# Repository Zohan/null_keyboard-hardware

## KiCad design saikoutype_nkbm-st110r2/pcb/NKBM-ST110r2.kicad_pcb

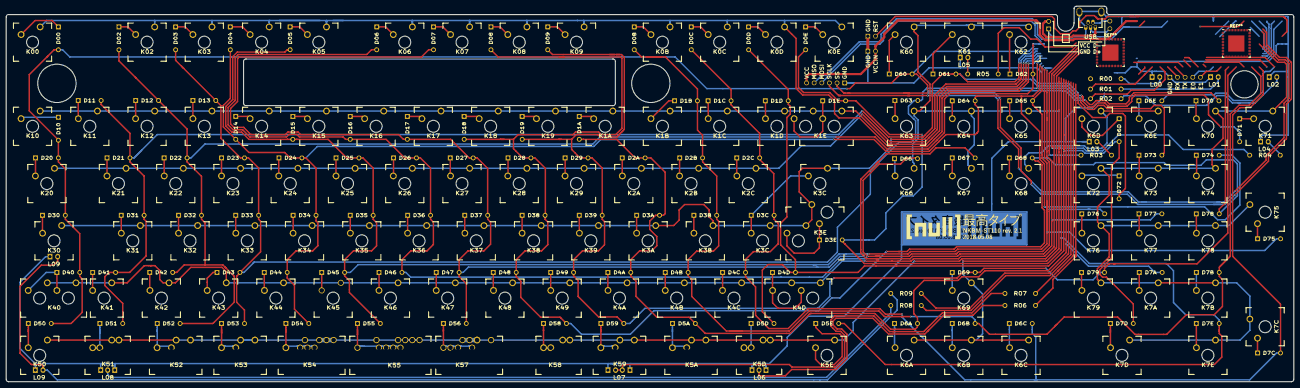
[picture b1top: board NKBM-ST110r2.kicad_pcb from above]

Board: 2 copper layers, 428.4 x 124.9 mm, 273 parts (0 on the bottom side), 146 nets.

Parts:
D00, D0B, D0C, D0D, D0E, D1A, D1B, D1C, D1D, D1E, D02, D2A, D2B, D2C, D03, D3A, D3B, D3C, D3E, D04, D4A, D4B, D4C, D4D, D05, D5A, D5D, D5E, D06, D6A, D6B, D6C, D6D, D6E, D07, D7A, D7B, D7C, D7D, D7E, D08, D09, D10, D11, D12, D13, D14, D15, D16, D17, D18, D19, D20, D21, D22, D23, D24, D25, D26, D27, D28, D29, D30, D31, D32, D33, D34, D35, D36, D37, D38, D39, D40, D41, D42, D43, D44, D45, D46, D47, D48, D49, D50, D51, D52, D53, D54, D55, D56, D58, D59, D60, D61, D62, D63, D64, D65, D66, D67, D68, D69, D70, D71, D72, D73, D74, D75, D76, D77, D78, D79: 1N4148; DIODE
EXPANSION: HEADER; TEENSY2.0++
K00, K0B, K0C, K0D, K0E, K1A, K1B, K1C, K1D, K1E2, K02, K2A, K2B, K2C, K03, K3A, K3B, K04, K4A, K4B, K4C, K05, K5D, K06, K6A, K6B, K6C, K6D, K6E, K07, K7A, K7B, K7E, K08, K09, K10, K11, K12, K13, K14, K15, K16, K17, K18, K19, K21, K22, K23, K24, K25, K26, K27, K28, K29, K31, K32, K33, K34, K35, K36, K37, K38, K39, K41, K42, K43, K44, K46, K47, K48, K49, K51, K53, K58#2, K60, K61, K62, K63, K64, K65, K66, K67, K68, K69, K70, K71, K72, K73, K74, K76, K77, K78, K79: CHRY_MX; CHERRY_PLATE_100H
K1E, K3E, K7D, K54, K57: CHRY_MX; CHERRY_PLATE_200H
K3C, K3C#2, K20: CHRY_MX; CHERRY_PLATE_150H
K3E2, K40, K542, K573: CHRY_MX; CHERRY_PLATE_225H
K4D, K30: CHRY_MX; CHERRY_PLATE_175H
K4D2: CHRY_MX; CHERRY_PLATE_275H
K5A, K5A1, K5D1, K5E, K45, K50, K52, K58, K59, K402, K511, K521, K521#2, K521#3, K541, K551, K553, K553#2, K572, K572#2, K591: CHRY_MX; CHERRY_PLATE_125H
K7C, K75: CHRY_MX; CHERRY_PLATE_200V
K55: CHRY_MX; CHERRY_PLATE_625H
K552: CHRY_MX; CHERRY_PLATE_450H
L00, L01, L02, L03, L04, L05, L07, L07#2, L09, L09#2: LED; LED_3MM
L06, L08: LED; LED_3MM1
R00, R01, R02, R03, R04, R05, R06, R07, R08, R09: R; RESISTOR
RST: HEADER; TEENSY2.0++
SPI: HEADER; TEENSY2.0++
USB: Molex USB_Mini-B; USB_Mini-B_Lumberg_2486_01_Horizontal
USB DATA: BREAKOUT; TEENSY2.0++
USB POWER: BREAKOUT; TEENSY2.0++
VCCIN: HEADER; TEENSY2.0++

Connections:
/COL_00: D00.2, D10.2, D20.2, D30.2, D40.2, D50.2, D60.2, D70.2
/COL_01: D11.2, D21.2, D31.2, D41.2, D51.2, D61.2, D71.2
/COL_02: D02.2, D12.2, D22.2, D32.2, D42.2, D52.2, D62.2, D72.2
/COL_03: D03.2, D13.2, D23.2, D33.2, D43.2, D53.2, D63.2, D73.2
/COL_04: D04.2, D14.2, D24.2, D34.2, D44.2, D54.2, D64.2, D74.2
/COL_05: D05.2, D15.2, D25.2, D35.2, D45.2, D55.2, D65.2, D75.2
/COL_06: D06.2, D16.2, D26.2, D36.2, D46.2, D66.2, D76.2
/COL_07: D07.2, D17.2, D27.2, D37.2, D47.2, D56.2, D67.2, D77.2
/COL_08: D08.2, D18.2, D28.2, D38.2, D48.2, D58.2, D68.2, D78.2
/COL_09: D09.2, D19.2, D29.2, D39.2, D49.2, D59.2, D69.2, D79.2
/COL_10: D1A.2, D2A.2, D3A.2, D4A.2, D5A.2, D6A.2, D7A.2
/COL_11: D0B.2, D1B.2, D2B.2, D3B.2, D4B.2, D6B.2, D7B.2
/COL_12: D0C.2, D1C.2, D2C.2, D3C.2, D4C.2, D6C.2, D7C.2
/COL_13: D0D.2, D1D.2, D4D.2, D5D.2, D6D.2, D7D.2
/COL_14: D0E.2, D1E.2, D3E.2, D5E.2, D6E.2, D7E.2
/GND: EXPANSION.1, L00.1, L01.1, L02.1, L03.1, L04.1, L05.1, L06.1, L07.1, L07#2.1, L08.1, L09.1, L09#2.1, RST.1, SPI.6, USB.1, USB.6, USB.7, USB POWER.1, VCCIN.1
/ROW_00: K00.1, K0B.1, K0C.1, K0D.1, K0E.1, K02.1, K03.1, K04.1, K05.1, K06.1, K07.1, K08.1, K09.1
/ROW_01: K1A.1, K1B.1, K1C.1, K1D.1, K1E.1, K1E2.1, K10.1, K11.1, K12.1, K13.1, K14.1, K15.1, K16.1, K17.1, K18.1, K19.1
/ROW_02: K2A.1, K2B.1, K2C.1, K20.1, K21.1, K22.1, K23.1, K24.1, K25.1, K26.1, K27.1, K28.1, K29.1
/ROW_03: K3A.1, K3B.1, K3C.1, K3C#2.1, K3E.1, K3E2.1, K30.1, K31.1, K32.1, K33.1, K34.1, K35.1, K36.1, K37.1, K38.1, K39.1
/ROW_04: K4A.1, K4B.1, K4C.1, K4D.1, K4D2.1, K40.1, K41.1, K42.1, K43.1, K44.1, K45.1, K46.1, K47.1, K48.1, K49.1, K402.1
/ROW_05: K5A.1, K5A1.1, K5D.1, K5D1.1, K5E.1, K50.1, K51.1, K52.1, K53.1, K54.1, K55.1, K57.1, K58.1, K58#2.1, K59.1, K511.1, K521.1, K521#2.1, K521#3.1, K541.1, K542.1, K551.1, K552.1, K553.1, K553#2.1, K572.1, K572#2.1, K573.1, K591.1
/ROW_06: K6A.1, K6B.1, K6C.1, K6D.1, K6E.1, K60.1, K61.1, K62.1, K63.1, K64.1, K65.1, K66.1, K67.1, K68.1, K69.1
/ROW_07: K7A.1, K7B.1, K7C.1, K7D.1, K7E.1, K70.1, K71.1, K72.1, K73.1, K74.1, K75.1, K76.1, K77.1, K78.1, K79.1
/VCC: SPI.1, VCCIN.2
unnamed: D0B.1, K0B.2
unnamed: D0C.1, K0C.2
unnamed: D0D.1, K0D.2
unnamed: D0E.1, K0E.2
unnamed: D00.1, K00.2
unnamed: D1A.1, K1A.2
unnamed: D1B.1, K1B.2
unnamed: D1C.1, K1C.2
unnamed: D1D.1, K1D.2
unnamed: D1E.1, K1E.2, K1E2.2
unnamed: D2A.1, K2A.2
unnamed: D2B.1, K2B.2
unnamed: D2C.1, K2C.2
unnamed: D3A.1, K3A.2
unnamed: D3B.1, K3B.2
unnamed: D3C.1, K3C.2, K3C#2.2
unnamed: D3E.1, K3E.2, K3E2.2
unnamed: D4A.1, K4A.2
unnamed: D4B.1, K4B.2
unnamed: D4C.1, K4C.2
unnamed: D4D.1, K4D.2, K4D2.2
unnamed: D5A.1, K5A.2, K5A1.2
unnamed: D5D.1, K5D.2, K5D1.2
unnamed: D5E.1, K5E.2
unnamed: D6A.1, K6A.2
unnamed: D6B.1, K6B.2
unnamed: D6C.1, K6C.2
unnamed: D6D.1, K6D.2
unnamed: D6E.1, K6E.2
unnamed: D7A.1, K7A.2
unnamed: D7B.1, K7B.2
unnamed: D7C.1, K7C.2
unnamed: D7D.1, K7D.2
unnamed: D7E.1, K7E.2
unnamed: D02.1, K02.2
unnamed: D03.1, K03.2
unnamed: D04.1, K04.2
unnamed: D05.1, K05.2
unnamed: D06.1, K06.2
unnamed: D07.1, K07.2
unnamed: D08.1, K08.2
unnamed: D09.1, K09.2
unnamed: D10.1, K10.2
unnamed: D11.1, K11.2
unnamed: D12.1, K12.2
unnamed: D13.1, K13.2
unnamed: D14.1, K14.2
unnamed: D15.1, K15.2
unnamed: D16.1, K16.2
unnamed: D17.1, K17.2
unnamed: D18.1, K18.2
unnamed: D19.1, K19.2
unnamed: D20.1, K20.2
unnamed: D21.1, K21.2
unnamed: D22.1, K22.2
unnamed: D23.1, K23.2
unnamed: D24.1, K24.2
unnamed: D25.1, K25.2
unnamed: D26.1, K26.2
unnamed: D27.1, K27.2
unnamed: D28.1, K28.2
unnamed: D29.1, K29.2
unnamed: D30.1, K30.2
unnamed: D31.1, K31.2
unnamed: D32.1, K32.2
unnamed: D33.1, K33.2
unnamed: D34.1, K34.2
unnamed: D35.1, K35.2
unnamed: D36.1, K36.2
unnamed: D37.1, K37.2
unnamed: D38.1, K38.2
unnamed: D39.1, K39.2
unnamed: D40.1, K40.2, K402.2
unnamed: D41.1, K41.2
unnamed: D42.1, K42.2
unnamed: D43.1, K43.2
unnamed: D44.1, K44.2
unnamed: D45.1, K45.2
unnamed: D46.1, K46.2
unnamed: D47.1, K47.2
unnamed: D48.1, K48.2
unnamed: D49.1, K49.2
unnamed: D50.1, K50.2
unnamed: D51.1, K51.2, K511.2
unnamed: D52.1, K52.2, K521.2
unnamed: D53.1, K53.2, K521#2.2
unnamed: D54.1, K54.2, K521#3.2, K541.2, K542.2
unnamed: D55.1, K55.2, K551.2, K552.2, K553.2, K553#2.2
unnamed: D56.1, K57.2, K572.2, K572#2.2, K573.2
unnamed: D58.1, K58.2, K58#2.2
unnamed: D59.1, K59.2, K591.2
unnamed: D60.1, K60.2
unnamed: D61.1, K61.2
unnamed: D62.1, K62.2
unnamed: D63.1, K63.2
unnamed: D64.1, K64.2
unnamed: D65.1, K65.2
unnamed: D66.1, K66.2
unnamed: D67.1, K67.2
unnamed: D68.1, K68.2
unnamed: D69.1, K69.2
unnamed: D70.1, K70.2
unnamed: D71.1, K71.2
unnamed: D72.1, K72.2
unnamed: D73.1, K73.2
unnamed: D74.1, K74.2
unnamed: D75.1, K75.2
unnamed: D76.1, K76.2
unnamed: D77.1, K77.2
unnamed: D78.1, K78.2
unnamed: D79.1, K79.2
unnamed: L00.2, R00.2
unnamed: L01.2, R01.2
unnamed: L02.2, R02.2
unnamed: L03.2, R03.2
unnamed: L04.2, R04.2
unnamed: L05.2, R05.2
unnamed: L06.2, R06.2
unnamed: L07.2, L07#2.2, R07.2
unnamed: L08.2, R08.2
unnamed: L09.2, L09#2.2, R09.2

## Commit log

2021-01-31 Begin conversion to 最悪ゴミ
2021-01-31 Add Net Labels
2021-02-14 Initial rotary. Build out all USB lanes
